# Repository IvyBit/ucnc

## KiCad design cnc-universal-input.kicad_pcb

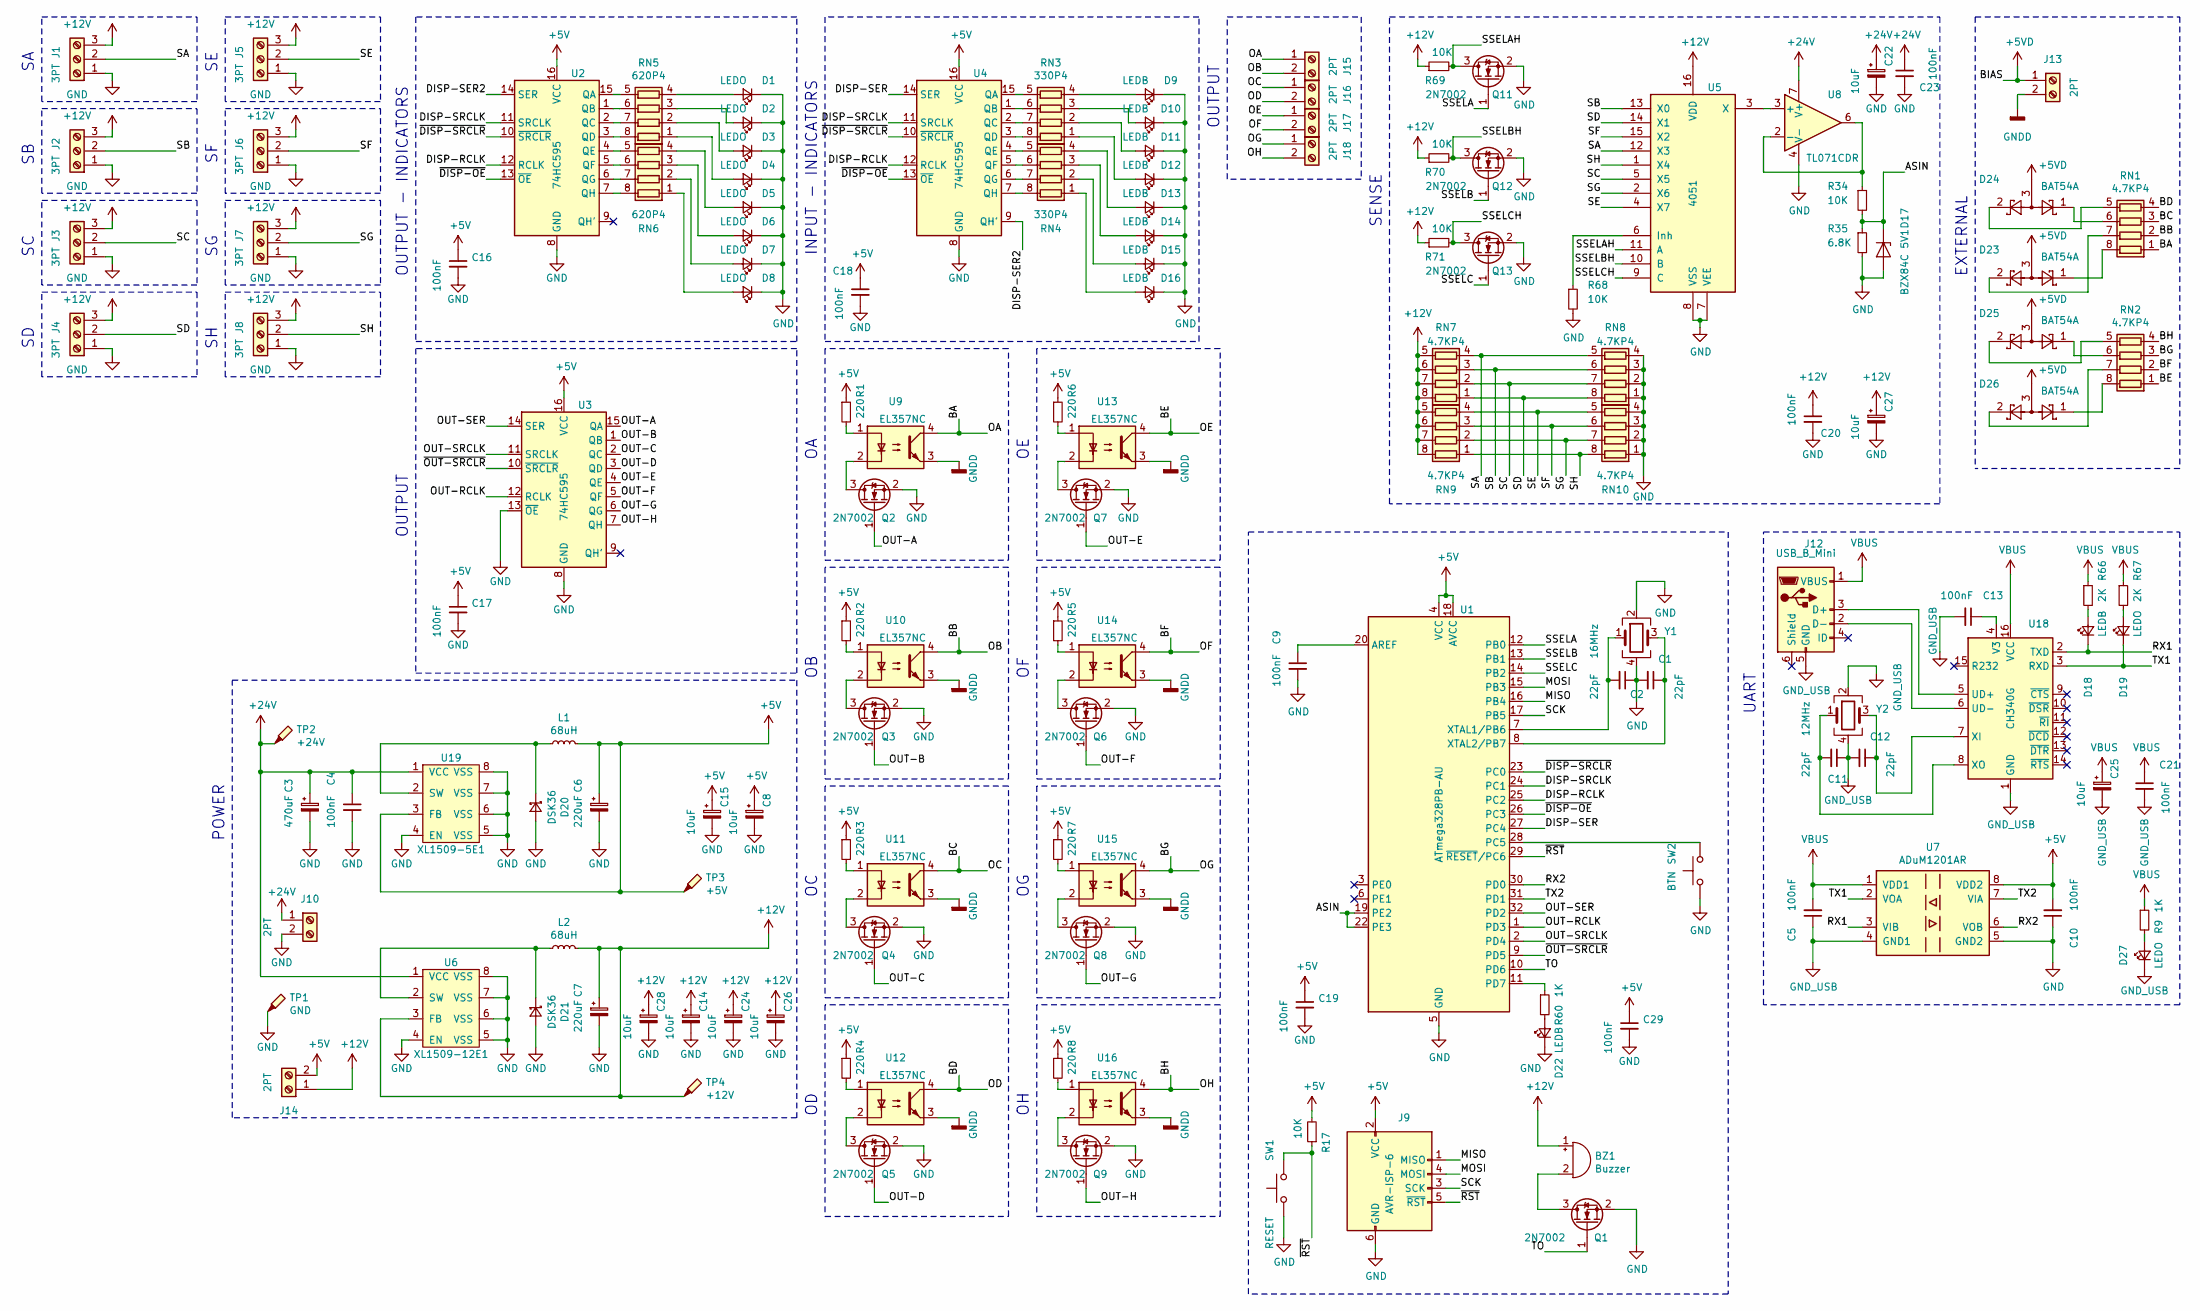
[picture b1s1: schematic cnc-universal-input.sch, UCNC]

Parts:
BZ1: Buzzer; Buzzer_15x7.5RM7.6; LCSC C128017
C1, C2, C11, C12: 22pF; C_0805_2012Metric; LCSC C1804
C3: 470uF; CP_Elec_10x10; LCSC C3350
C4, C5, C9, C10, C13, C16, C17, C18, C19, C20, C21, C23, C29: 100nF; C_0805_2012Metric; LCSC C49678
C6, C7: 220uF; CP_Elec_6.3x7.7; LCSC C3342
C8, C14, C15, C22, C24, C25, C26, C27, C28: 10uF; C_1206_3216Metric; LCSC C13585
D1, D2, D3, D4, D5, D6, D7, D8, D19, D27: LEDO; D_0805_2012Metric; LCSC C205444
D9, D10, D11, D12, D13, D14, D15, D16, D18, D22: LEDB; D_0805_2012Metric; LCSC C205441
D17: BZX84C 5V1; D_SOT-23_ANK; LCSC C294621
D20, D21: DSK36; D_SOD-123F; LCSC C106913
D23, D24, D25, D26: BAT54A; SOT-23; LCSC C556167
J1, J2, J3, J4, J5, J6, J7, J8: 3PT; TerminalBlock_RND_205-00013_1x03_P5.00mm_Horizontal; LCSC C8270
J9: AVR-ISP-6; PinHeader_2x03_P2.54mm_Vertical_SMD; LCSC C192301
J10, J13, J14, J15, J16, J17, J18: 2PT; TerminalBlock_RND_205-00001_1x02_P5.00mm_Horizontal; LCSC C8404
J12: USB_B_Mini; USB_Mini-B_Lumberg_2486_01_Horizontal; LCSC C1121886
L1, L2: 68uH; L_12x12mm_H8mm; LCSC C169377
Q1, Q2, Q3, Q4, Q5, Q6, Q7, Q8, Q9, Q11, Q12, Q13: 2N7002; SOT-23; LCSC C8545
R1, R2, R3, R4, R5, R6, R7, R8: 220; R_0805_2012Metric; LCSC C17557
R9, R60: 1K; R_0805_2012Metric; LCSC C17513
R17, R34, R68, R69, R70, R71: 10K; R_0805_2012Metric; LCSC C17724
R35: 6.8K; R_0805_2012Metric; LCSC C17772
R66, R67: 2K; R_0805_2012Metric; LCSC C17604
RN1, RN2, RN7, RN8, RN9, RN10: 4.7KP4; R_Array_Convex_4x0603; LCSC C66697
RN3, RN4: 330P4; R_Array_Convex_4x0603; LCSC C12018
RN5, RN6: 620P4; R_Array_Convex_4x0603; LCSC C12034
SW1: RESET; SW_SPST_TL3342; LCSC C318884
SW2: BTN; SW_SPST_TL3342; LCSC C318884
TP1: GND; TestPoint_Pad_D1.5mm
TP2: +24V; TestPoint_Pad_D1.5mm
TP3: +5V; TestPoint_Pad_D1.5mm
TP4: +12V; TestPoint_Pad_D1.5mm
U1: ATmega328PB-AU; TQFP-32_7x7mm_P0.8mm; LCSC C132230
U2, U3, U4: 74HC595; SOIC-16_3.9x9.9mm_P1.27mm; LCSC C5947
U5: 4051; SOIC-16_3.9x9.9mm_P1.27mm; LCSC C21379
U6: XL1509-12E1; SOIC-8_3.9x4.9mm_P1.27mm; LCSC C62594
U7: ADuM1201AR; SOIC-8_3.9x4.9mm_P1.27mm; LCSC C9669
U8: TL071CDR; SOIC-8_3.9x4.9mm_P1.27mm; LCSC C14449
U9, U10, U11, U12, U13, U14, U15, U16: EL357NC; SO-4_4.4x3.9mm_P2.54mm; LCSC C29981
U18: CH340G; SOIC-16_3.9x9.9mm_P1.27mm; LCSC C14267
U19: XL1509-5E1; SOIC-8_3.9x4.9mm_P1.27mm; LCSC C61063
Y1: 16MHz; Crystal_SMD_3225-4Pin_3.2x2.5mm; LCSC C13738
Y2: 12MHz; Crystal_SMD_3225-4Pin_3.2x2.5mm; LCSC C9002

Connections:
+5V: C6.1, C8.1, C10.2, C15.1, C16.1, C17.1, C18.1, C19.1, C29.1, J9.2 (VCC), J14.2, L1.2, R1.1, R2.1, R3.1, R4.1, R5.1, R6.1, R7.1, R8.1, R17.2, TP3.1, U1.4 (VCC), U1.18 (AVCC), U2.16 (VCC), U3.16 (VCC), U4.16 (VCC), U7.8 (VDD2), U19.3 (FB)
+5VD: D23.3, D24.3, D25.3, D26.3, J13.1
+12V: BZ1.1 (-), C7.1, C14.1, C20.1, C24.1, C26.1, C27.1, C28.1, J1.3, J2.3, J3.3, J4.3, J5.3, J6.3, J7.3, J8.3, J14.1, L2.2, R69.1, R70.1, R71.1, RN7.5 (R4.2), RN7.6 (R3.2), RN7.7 (R2.2), RN7.8 (R1.2), RN9.5 (R4.2), RN9.6 (R3.2), RN9.7 (R2.2), RN9.8 (R1.2), TP4.1, U5.16 (VDD), U6.3 (FB)
+24V: C3.1, C4.1, C22.1, C23.1, J10.1, TP2.1, U6.1 (VCC), U8.7 (V+), U19.1 (VCC)
/ASIN: D17.1 (K), R34.2, R35.1, U1.19 (PE2), U1.22 (PE3)
/BA: J15.1, RN1.1 (R1.1), U9.4
/BB: J15.2, RN1.2 (R2.1), U10.4
/BC: J16.1, RN1.3 (R3.1), U11.4
/BD: J16.2, RN1.4 (R4.1), U12.4
/BE: J17.1, RN2.1 (R1.1), U13.4
/BF: J17.2, RN2.2 (R2.1), U14.4
/BG: J18.1, RN2.3 (R3.1), U15.4
/BH: J18.2, RN2.4 (R4.1), U16.4
/DISP-RCLK: U1.25 (PC2), U2.12 (RCLK), U4.12 (RCLK)
/DISP-SER: U1.27 (PC4), U4.14 (SER)
/DISP-SER2: U2.14 (SER), U4.9 (QH')
/DISP-SRCLK: U1.24 (PC1), U2.11 (SRCLK), U4.11 (SRCLK)
/MISO: J9.1 (MISO), U1.16 (PB4)
/MOSI: J9.4 (MOSI), U1.15 (PB3)
/OUT-A: Q2.1 (G), U3.15 (QA)
/OUT-B: Q3.1 (G), U3.1 (QB)
/OUT-C: Q4.1 (G), U3.2 (QC)
/OUT-D: Q5.1 (G), U3.3 (QD)
/OUT-E: Q7.1 (G), U3.4 (QE)
/OUT-F: Q6.1 (G), U3.5 (QF)
/OUT-G: Q8.1 (G), U3.6 (QG)
/OUT-H: Q9.1 (G), U3.7 (QH)
/OUT-RCLK: U1.1 (PD3), U3.12 (RCLK)
/OUT-SER: U1.32 (PD2), U3.14 (SER)
/OUT-SRCLK: U1.2 (PD4), U3.11 (SRCLK)
/RX1: D18.1 (K), U7.3 (VIB), U18.2 (TXD)
/RX2: U1.30 (PD0), U7.6 (VOB)
/SA: J1.2, RN7.4 (R4.1), RN8.5 (R4.2), U5.12 (X3)
/SB: J2.2, RN7.3 (R3.1), RN8.6 (R3.2), U5.13 (X0)
/SC: J3.2, RN7.2 (R2.1), RN8.7 (R2.2), U5.5 (X5)
/SCK: J9.3 (SCK), U1.17 (PB5)
/SD: J4.2, RN7.1 (R1.1), RN8.8 (R1.2), U5.14 (X1)
/SE: J5.2, RN9.4 (R4.1), RN10.5 (R4.2), U5.4 (X7)
/SF: J6.2, RN9.3 (R3.1), RN10.6 (R3.2), U5.15 (X2)
/SG: J7.2, RN9.2 (R2.1), RN10.7 (R2.2), U5.2 (X6)
/SH: J8.2, RN9.1 (R1.1), RN10.8 (R1.2), U5.1 (X4)
/SSELA: Q11.1 (G), U1.12 (PB0)
/SSELAH: Q11.3 (D), R69.2, U5.11 (A)
/SSELB: Q12.1 (G), U1.13 (PB1)
/SSELBH: Q12.3 (D), R70.2, U5.10 (B)
/SSELC: Q13.1 (G), U1.14 (PB2)
/SSELCH: Q13.3 (D), R71.2, U5.9 (C)
/TO: Q1.1 (G), U1.10 (PD6)
/TX1: D19.1 (K), U7.2 (VOA), U18.3 (RXD)
/TX2: U1.31 (PD1), U7.7 (VIA)
/~DISP-OE: U1.26 (PC3), U2.13 (~OE), U4.13 (~OE)
/~DISP-SRCLR: U1.23 (PC0), U2.10 (~SRCLR), U4.10 (~SRCLR)
/~OUT-SRCLR: U1.9 (PD5), U3.10 (~SRCLR)
/~RST: J9.5 (~RST), R17.1, SW1.2, U1.29 (~RESET~/PC6)
GND: C1.2, C2.1, C3.2, C4.2, C6.2, C7.2, C8.2, C9.2, C10.1, C14.2, C15.2, C16.2, C17.2, C18.2, C19.2, C20.2, C22.2, C23.2, C24.2, C26.2, C27.2, C28.2, C29.2, D1.1 (K), D2.1 (K), D3.1 (K), D4.1 (K), D5.1 (K), D6.1 (K), D7.1 (K), D8.1 (K), D9.1 (K), D10.1 (K), D11.1 (K), D12.1 (K), D13.1 (K), D14.1 (K), D15.1 (K), D16.1 (K), D17.2 (A), D20.2 (A), D21.2 (A), D22.1 (K), J1.1, J2.1, J3.1, J4.1, J5.1, J6.1, J7.1, J8.1, J9.6 (GND), J10.2, Q1.2 (S), Q2.2 (S), Q3.2 (S), Q4.2 (S), Q5.2 (S), Q6.2 (S), Q7.2 (S), Q8.2 (S), Q9.2 (S), Q11.2 (S), Q12.2 (S), Q13.2 (S), R35.2, R68.2, RN8.1 (R1.1), RN8.2 (R2.1), RN8.3 (R3.1), RN8.4 (R4.1), RN10.1 (R1.1), RN10.2 (R2.1), RN10.3 (R3.1), RN10.4 (R4.1), SW1.1, SW2.1, TP1.1, U1.5 (GND), U1.21 (GND), U2.8 (GND), U3.8 (GND), U3.13 (~OE), U4.8 (GND), U5.7 (VEE), U5.8 (VSS), U6.4 (EN), U6.5 (VSS), U6.6 (VSS), U6.7 (VSS), U6.8 (VSS), U7.5 (GND2), U8.4 (V-), U19.4 (EN), U19.5 (VSS), U19.6 (VSS), U19.7 (VSS), U19.8 (VSS), Y1.2, Y1.4
GNDD: J13.2, U9.3, U10.3, U11.3, U12.3, U13.3, U14.3, U15.3, U16.3
GND_USB: C5.1, C11.1, C12.2, C13.2, C21.2, C25.2, D27.1 (K), J12.5 (GND), U7.4 (GND1), U18.1 (GND), Y2.2, Y2.4
unnamed: BZ1.2 (+), Q1.3 (D)
unnamed: C1.1, U1.8 (XTAL2/PB7), Y1.3
unnamed: C2.2, U1.7 (XTAL1/PB6), Y1.1
unnamed: C9.1, U1.20 (AREF)
unnamed: C11.2, U18.8 (XO), Y2.1
unnamed: C12.1, U18.7 (XI), Y2.3
unnamed: C13.1, U18.4 (V3)
unnamed: D1.2 (A), RN5.4 (R4.1)
unnamed: D2.2 (A), RN5.3 (R3.1)
unnamed: D3.2 (A), RN5.2 (R2.1)
unnamed: D4.2 (A), RN5.1 (R1.1)
unnamed: D5.2 (A), RN6.4 (R4.1)
unnamed: D6.2 (A), RN6.3 (R3.1)
unnamed: D7.2 (A), RN6.2 (R2.1)
unnamed: D8.2 (A), RN6.1 (R1.1)
unnamed: D9.2 (A), RN3.4 (R4.1)
unnamed: D10.2 (A), RN3.3 (R3.1)
unnamed: D11.2 (A), RN3.2 (R2.1)
unnamed: D12.2 (A), RN3.1 (R1.1)
unnamed: D13.2 (A), RN4.4 (R4.1)
unnamed: D14.2 (A), RN4.3 (R3.1)
unnamed: D15.2 (A), RN4.2 (R2.1)
unnamed: D16.2 (A), RN4.1 (R1.1)
unnamed: D18.2 (A), R66.2
unnamed: D19.2 (A), R67.2
unnamed: D20.1 (K), L1.1, U19.2 (SW)
unnamed: D21.1 (K), L2.1, U6.2 (SW)
unnamed: D22.2 (A), R60.2
unnamed: D23.1, RN1.8 (R1.2)
unnamed: D23.2, RN1.7 (R2.2)
unnamed: D24.1, RN1.6 (R3.2)
unnamed: D24.2, RN1.5 (R4.2)
unnamed: D25.1, RN2.6 (R3.2)
unnamed: D25.2, RN2.5 (R4.2)
unnamed: D26.1, RN2.8 (R1.2)
unnamed: D26.2, RN2.7 (R2.2)
unnamed: D27.2 (A), R9.2
unnamed: J12.2 (D-), U18.6 (UD-)
unnamed: J12.3 (D+), U18.5 (UD+)
unnamed: Q2.3 (D), U9.2
unnamed: Q3.3 (D), U10.2
unnamed: Q4.3 (D), U11.2
unnamed: Q5.3 (D), U12.2
unnamed: Q6.3 (D), U14.2
unnamed: Q7.3 (D), U13.2
unnamed: Q8.3 (D), U15.2
unnamed: Q9.3 (D), U16.2
unnamed: R1.2, U9.1
unnamed: R2.2, U10.1
unnamed: R3.2, U11.1
unnamed: R4.2, U12.1
unnamed: R5.2, U14.1
unnamed: R6.2, U13.1
unnamed: R7.2, U15.1
unnamed: R8.2, U16.1
unnamed: R34.1, U8.2 (-), U8.6
unnamed: R60.1, U1.11 (PD7)
unnamed: R68.1, U5.6 (Inh)
unnamed: RN3.5 (R4.2), U4.15 (QA)
unnamed: RN3.6 (R3.2), U4.1 (QB)
unnamed: RN3.7 (R2.2), U4.2 (QC)
unnamed: RN3.8 (R1.2), U4.3 (QD)
unnamed: RN4.5 (R4.2), U4.4 (QE)
unnamed: RN4.6 (R3.2), U4.5 (QF)
unnamed: RN4.7 (R2.2), U4.6 (QG)
unnamed: RN4.8 (R1.2), U4.7 (QH)
unnamed: RN5.5 (R4.2), U2.15 (QA)
unnamed: RN5.6 (R3.2), U2.1 (QB)
unnamed: RN5.7 (R2.2), U2.2 (QC)
unnamed: RN5.8 (R1.2), U2.3 (QD)
unnamed: RN6.5 (R4.2), U2.4 (QE)
unnamed: RN6.6 (R3.2), U2.5 (QF)
unnamed: RN6.7 (R2.2), U2.6 (QG)
unnamed: RN6.8 (R1.2), U2.7 (QH)
unnamed: SW2.2, U1.28 (PC5)
unnamed: U5.3 (X), U8.3 (+)
VBUS: C5.2, C21.1, C25.1, J12.1 (VBUS), R9.1, R66.1, R67.1, U7.1 (VDD1), U18.16 (VCC)

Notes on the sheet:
POWER
INPUT - INDICATORS
OUTPUT - INDICATORS
SENSE
EXTERNAL
OUTPUT
UART

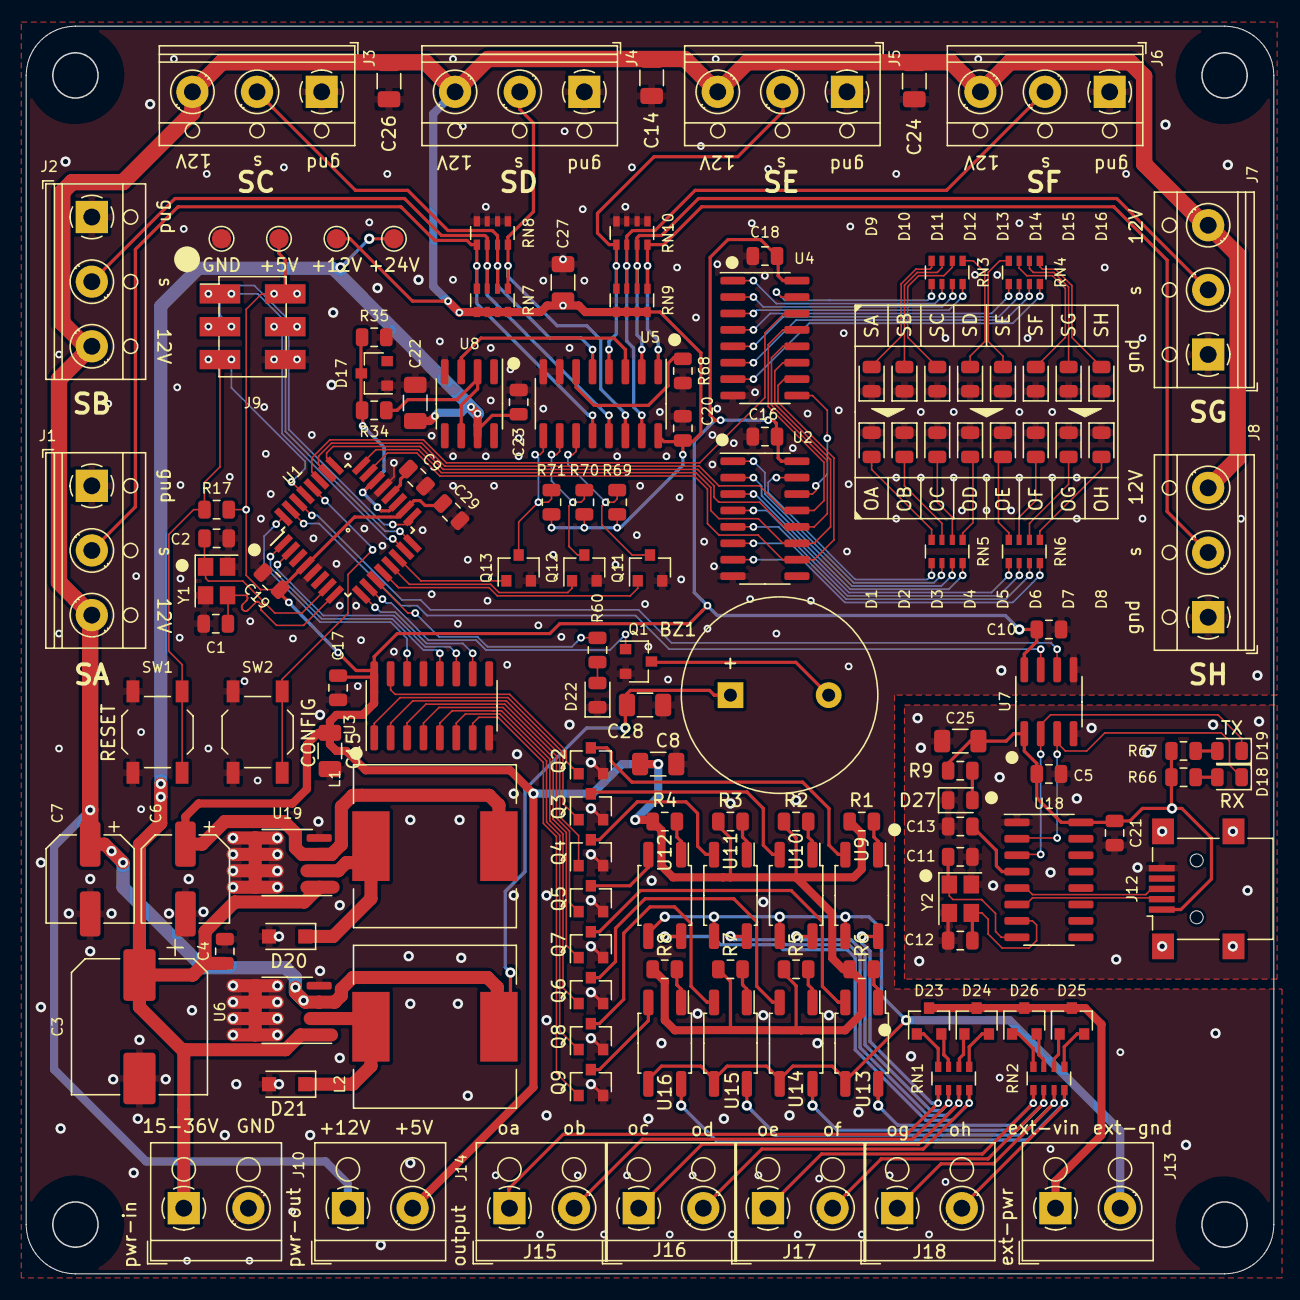
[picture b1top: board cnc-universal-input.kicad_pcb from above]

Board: 2 copper layers, 96.5 x 96.5 mm, 143 parts (0 on the bottom side), 134 nets.

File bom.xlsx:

Column1 | Column2 | Column3 | Column4
Comment | Designator | Footprint | LCSC
Buzzer | BZ1 | Buzzer_Beeper:Buzzer_15x7.5RM7.6 | C128017
22pF | C1,C2,C11,C12 | Capacitor_SMD:C_0805_2012Metric | C1804
100nF | C4,C5,C9,C10,C13,C16,C17,C18,C19,C20,C21,C23,C29 | Capacitor_SMD:C_0805_2012Metric | C49678
10uF | C8,C14,C15,C22,C24,C25,C26,C27,C28 | Capacitor_SMD:C_1206_3216Metric | C13585
470uF | C3 | Capacitor_SMD:CP_Elec_10x10 | C3350
220uF | C6,C7 | Capacitor_SMD:CP_Elec_6.3x7.7 | C3342
LEDO | D1,D2,D3,D4,D5,D6,D7,D8,D19,D27 | Diode_SMD:D_0805_2012Metric | C205444
BZX84C 5V1 | D17 | Diode_SMD:D_SOT-23_ANK | C294621
SS36-E3/57T | D20,D21 | Diode_SMD:D_2114_3652Metric | C35722
BAT54A | D23,D24,D25,D26 | Package_TO_SOT_SMD:SOT-23 | C556167
LEDB | D9,D10,D11,D12,D13,D14,D15,D16,D18,D22 | Diode_SMD:D_0805_2012Metric | C205441
3PT | J1,J2,J3,J4,J5,J6,J7,J8 | TerminalBlock_RND:TerminalBlock_RND_205-00013_1x03_P5.00mm_Horizontal | C8270
USB_B_Mini | J12 | Connector_USB:USB_Mini-B_Lumberg_2486_01_Horizontal | C1121886
2PT | J10,J13,J14,J15,J16,J17,J18 | TerminalBlock_RND:TerminalBlock_RND_205-00001_1x02_P5.00mm_Horizontal | C8404
AVR-ISP-6 | J9 | Connector_PinHeader_2.54mm:PinHeader_2x03_P2.54mm_Vertical_SMD | C192301
68uH | L1,L2 | Inductor_SMD:L_12x12mm_H8mm | C169377
2N7002 | Q1,Q2,Q3,Q4,Q5,Q6,Q7,Q8,Q9,Q11,Q12,Q13 | Package_TO_SOT_SMD:SOT-23 | C8545
220 | R1,R2,R3,R4,R5,R6,R7,R8 | Resistor_SMD:R_0805_2012Metric | C17557
10K | R17,R34,R68,R69,R70,R71 | Resistor_SMD:R_0805_2012Metric | C17724
6.8K | R35 | Resistor_SMD:R_0805_2012Metric | C17772
1K | R9,R60 | Resistor_SMD:R_0805_2012Metric | C17513
2K | R66,R67 | Resistor_SMD:R_0805_2012Metric | C17604
4.7KP4 | RN1,RN2,RN7,RN8,RN9,RN10 | Resistor_SMD:R_Array_Convex_4x0603 | C66697
330P4 | RN3,RN4 | Resistor_SMD:R_Array_Convex_4x0603 | C12018
620P4 | RN5,RN6 | Resistor_SMD:R_Array_Convex_4x0603 | C12034
RESET | SW1 | Button_Switch_SMD:SW_SPST_TL3342 | C318884
BTN | SW2 | Button_Switch_SMD:SW_SPST_TL3342 | C318884
GND | TP1 | TestPoint:TestPoint_Pad_D1.5mm
+24V | TP2 | TestPoint:TestPoint_Pad_D1.5mm
+5V | TP3 | TestPoint:TestPoint_Pad_D1.5mm
+12V | TP4 | TestPoint:TestPoint_Pad_D1.5mm
ATmega328PB-AU | U1 | Package_QFP:TQFP-32_7x7mm_P0.8mm | C132230
CH340G | U18 | Package_SO:SOIC-16_3.9x9.9mm_P1.27mm | C14267
XL1509-5E1 | U19 | Package_SO:SOIC-8_3.9x4.9mm_P1.27mm | C61063
74HC595 | U2,U3,U4 | Package_SO:SOIC-16_3.9x9.9mm_P1.27mm | C5947
4051 | U5 | Package_SO:SOIC-16_3.9x9.9mm_P1.27mm | C21379
XL1509-12E1 | U6 | Package_SO:SOIC-8_3.9x4.9mm_P1.27mm | C62594
ADuM1201AR | U7 | Package_SO:SOIC-8_3.9x4.9mm_P1.27mm | C9669
SGMOP07CXS8G/TR | U8 | Package_SO:SOIC-8_3.9x4.9mm_P1.27mm | C89712
EL357NC | U9,U10,U11,U12,U13,U14,U15,U16 | IvyBit-footprints:SOP-4_4.1x4.4x2.54P | C29981
16MHz | Y1 | Crystal:Crystal_SMD_3225-4Pin_3.2x2.5mm | C13738
12MHz | Y2 | Crystal:Crystal_SMD_3225-4Pin_3.2x2.5mm | C9002

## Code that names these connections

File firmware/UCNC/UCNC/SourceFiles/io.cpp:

/*
 * io.cpp
 *
 * Created: 06.06.2021 00:01:02
 *  Author: alrha
 */

#include "definitions.h"
#include "io.h"

#include <avr/io.h>
#include <avr/interrupt.h>
#include <avr/wdt.h>
#include <util/delay.h>
#include <avr/pgmspace.h>
#include <avr/eeprom.h>



#define DISP_SRCLR	(PINC0)
#define DISP_SRCLK	(PINC1)
#define DISP_RCLK	(PINC2)
#define DISP_OE		(PINC3)
#define DISP_SER	(PINC4)

#define BTN_AUX		(PINC5)
#define BTN_RESET	(PINC6)

#define	OUT_SER		(PIND2)
#define	OUT_RCLK	(PIND3)
#define	OUT_SRCLK	(PIND4)
#define	OUT_SRCLR	(PIND5)

#define	OUT_TONE	(PIND6)
#define	OUT_LED		(PIND7)


#define SSEL_A		(PINB0)
#define SSEL_B		(PINB1)
#define SSEL_C		(PINB2)
#define ASIN		(PINE2)




//inverted select signal
#define ASA	((uint8_t)(~0x03 & 0x07)) //011 -> 100 -> 0x04
#define ASB	((uint8_t)(~0x00 & 0x07)) //000 -> 111 -> 0x07
#define ASC	((uint8_t)(~0x05 & 0x07)) //101 -> 010 -> 0x02
#define ASD	((uint8_t)(~0x01 & 0x07)) //001 -> 110 -> 0x06
#define ASE	((uint8_t)(~0x07 & 0x07)) //111 -> 000 -> 0x00
#define ASF	((uint8_t)(~0x02 & 0x07)) //010 -> 101 -> 0x05
#define ASG	((uint8_t)(~0x06 & 0x07)) //110 -> 001 -> 0x01
#define ASH	((uint8_t)(~0x04 & 0x07)) //100 -> 011 -> 0x03




namespace io {

	const uint8_t ASI_MAP[8] PROGMEM= { ASA, ASB, ASC, ASD, ASE, ASF, ASG, ASH };
	uint32_t boot_cfg __attribute__ ((section (".noinit")));

	volatile uint8_t	adc_values[16]	= {0};
	volatile uint8_t*	adc_value_write	= nullptr;
	volatile uint8_t*	adc_value_read	= nullptr;
	volatile bool	    adc_busy		= false;

	void setup(){
		//make PINC0-4 outputs
		DDRC |= ((1 << DISP_SRCLR) | (1 << DISP_SRCLK) | (1 << DISP_RCLK) | (1 << DISP_OE) | (1 << DISP_SER));
		//make PC5 an input
		DDRC &= ~(1 << BTN_AUX);
		//set PORTC to low and enable pullup for PC5
		PORTC = (1 << BTN_AUX);
		//disable input clear
		PORTC |= (1 << DISP_SRCLR);
		//enable input indicators
		PORTC &= ~(1 << DISP_OE);

		//make PIND2-7 outputs
		DDRD |= ((1 << OUT_SER) | (1 << OUT_RCLK) | (1 << OUT_SRCLK) | (1 << OUT_SRCLR)| (1 << OUT_TONE) | (1 << OUT_LED) );
		//disable output clear
		PORTD |= (1 << OUT_SRCLR);
		//enable outputs
		//PORTD &= ~(1 << OUT_OE);

		//make PB0-PB2 outputs
		DDRB |= (1 << SSEL_A) |(1 << SSEL_B) |(1 << SSEL_C);

		DDRE = 0x00;
		PORTE |= (1 << PINE0) | (1 << PINE1);

		//select 5v reference input ADC6 and left align result
		ADMUX |= (1 << REFS0) | (1 << MUX2) | (1 << MUX1) | (1 << ADLAR);
		//enable ADC, enable interrupt, set prescaler to 16
		ADCSRA |= (1 << ADEN) | (1 << ADIE) | (1 << ADPS2)| (0 << ADPS1)| (0 << ADPS0);

		//select input A as adc source
		PORTB = (uint8_t)((PORTB & (uint8_t)~0x07) | pgm_read_byte(&ASI_MAP[0]));


		//TIMER 0 8BIT BUZZER TONE
		OCR0A = 70;
		TCCR0A |= (1 << COM0A0) | (1 << WGM01); //TOGGLE OC0A/PD6
		//TCCR0B |= (1 << CS01) | (1 << CS00);	//64 DIV PRESCLARER


		//TIMER1 16BIT BUZZER DELAY
		TCCR1A = 0x00;
		TCCR1B = (1 << WGM12); //CTC MODE NO CLOCK SOURCE
		TIMSK1 |= (1 << OCIE1A); //ENABLE TIMER1_COMPA INTERRUPT

		//TIMER3 16BIT LED
		TCCR3A = 0x00;
		TCCR3B = (1 << WGM32); //CTC MODE NO CLOCK SOURCE
		TIMSK3 |= (1 << OCIE3A); //ENABLE TIMER3_COMPA INTERRUPT



		//enable interrupts
		sei();
	}


	void set_indicators(uint16_t indicators){

		for (uint8_t i = 0; i < 16; i++)
		{
			//shift value into register
			if((indicators >> i) & 0x01){
				PORTC |= (1 << DISP_SER);
				}else{
				PORTC &= ~(1 << DISP_SER);
			}
			//clock register
			PORTC |= (1 << DISP_SRCLK);
			PORTC &= ~(1 << DISP_SRCLK);
		}

		//clock output register
		PORTC |= (1 << DISP_RCLK);
		PORTC &= ~(1 << DISP_RCLK);
	}

	void clear_indicators(){
		//clear register
		PORTC &= ~(1 << DISP_SRCLR);
		PORTC |= (1 << DISP_SRCLR);

		//clock output register
		PORTC |= (1 << DISP_RCLK);
		PORTC &= ~(1 << DISP_RCLK);
	}

	void set_outputs(uint8_t outputs){
		for (uint8_t i = 0; i < 8; i++)
		{
			//shift value into register
			if(((outputs >> i) & 0x01)){
				PORTD |= (1 << OUT_SER);
			}else{
				PORTD &= ~(1 << OUT_SER);
			}
			//clock register
			PORTD |= (1 << OUT_SRCLK);
			PORTD &= ~(1 << OUT_SRCLK);
		}

		//clock output register
		PORTD |= (1 << OUT_RCLK);
		PORTD &= ~(1 << OUT_RCLK);
	}

	void clear_outputs(){
		//clear register
		PORTD &= ~(1 << OUT_SRCLR);
		PORTD |= (1 << OUT_SRCLR);

		//clock output register
		PORTD |= (1 << OUT_RCLK);
		PORTD &= ~(1 << OUT_RCLK);
	}



	/*BUTTON*/
	ISR(PCINT1_vect){
		cli();
		set_boot_cfg_flag();
		reset_mcu();
	}

	bool get_aux_pushed(){
		return (PINC & (1 << BTN_AUX)) != (1 << BTN_AUX);
	}

	void enable_btn_reset_async(){
		PCMSK1 |= (1 << PCINT13);
		PCICR |= (1 << PCIE1);
	}

	void disable_btn_reset_async(){
		PCICR &= ~(1 << PCIE1);
		PCMSK1 &= ~(1 << PCINT13);
	}
	/*BUTTON*/


	/*ADC*/
	ISR(ADC_vect){

		static uint8_t		adc_index = 0;

		uint8_t current_index = adc_index;
		adc_index++;

		if(adc_index > 7) adc_index = 0;

		PORTB = (uint8_t)((PORTB & (uint8_t)~0x07) | pgm_read_byte(&ASI_MAP[adc_index]));

		uint8_t av = 0;

		//av |= ADCL;
		av = ADCH;//(uint16_t)(ADCH << 8);

		adc_value_write[current_index] = (uint8_t)(av * (100.0 / ADC_LIMIT));
		if(adc_value_write[current_index] > 100){
			adc_value_write[current_index] = 100;
		}

		if(adc_index < 7){
			//start conversion
			ADCSRA |= (1 << ADSC);
		}else{
			adc_busy = false;
		}
	}

	bool adc_is_busy(){
		return adc_busy;
	}

	void adc_busy_wait(){
		while(adc_busy){}
	}

	void adc_start_conversion(){

		adc_busy = true;

		//toggle adc target buffer
		if(adc_value_read != adc_values){
		   adc_value_read = &adc_values[0];
		   adc_value_write = &adc_values[8];
		}
		else{
			adc_value_read = &adc_values[8];
			adc_value_write = &adc_values[0];
		}

		//start conversion
		ADCSRA |= (1 << ADSC);
	}

	void adc_update(uint8_t (&buffer)[8]){
		for (uint8_t i = 0; i < 8; i++){
			buffer[i] = adc_value_read[i];
		}
	}
	/*ADC*/





	/*BUZZER*/
	ISR(TIMER1_COMPA_vect){
		//STOP TIMER 0 PRESCLAER
		TCCR1B = (1 << WGM12);
		//BUZZER OFF
		TCCR0B = 0x00;	//0 DIV PRESCALER
	}

	void buzzer_on_for(uint16_t milliseconds){
		if(milliseconds == 0xFFFF) milliseconds--;
		//BUZZER ON
		TCCR0B |= (1 << CS01) | (1 << CS00);	//64 DIV PRESCLARER
		//DUMB DELAY LOOP
		for (uint16_t i = 0; i < milliseconds; i++){
			_delay_ms(1);
		}
		//BUZZER OFF
		TCCR0B = 0x00;	//0 DIV PRESCLARER
	}

	void buzzer_on_for_async(uint16_t milliseconds){
		TCNT1 = 0x00;
		//((A3/B3) * C3 ) / 1000-1
		OCR1A = (((F_CPU / 1024.0) * milliseconds) / 1000.0) - 1;
		//OCR1A = (uint16_t)(milliseconds / (1000.0 / (F_CPU / 1024.0))) - 1;
		//START TIMER 1024 PRESCLAER
		TCCR1B |= ((1 <<CS12) | (1 << CS10));
		//BUZZER ON
		TCNT0 = 0x00;
		TCCR0B |= (1 << CS01) | (1 << CS00);	//64 DIV PRESCLARER
	}

	void buzzer_on(){
		TCNT0 = 0x00;
		TCCR0B |= (1 << CS01) | (1 << CS00);	//64 DIV PRESCLARER
	}

	void buzzer_on_off(){
		TCCR0B = 0x00;	//0 DIV PRESCLARER
	}
	/*BUZZER*/




	/*LED*/
	ISR(TIMER3_COMPA_vect){
		//STOP TIMER 0 PRESCLAER
		TCCR3B = (1 << WGM32);
		//BUZZER OFF
		PORTD &= ~(1 << OUT_LED);
	}

	void led_on_for(uint16_t milliseconds){
		if(milliseconds == 0xFFFF) milliseconds--;
		//BUZZER ON
		PORTD |= (1 << OUT_LED);
		//DUMB DELAY LOOP
		for (uint16_t i = 0; i < milliseconds; i++){
			_delay_ms(1);
		}
		//BUZZER OFF
		PORTD &= ~(1 << OUT_LED);
	}

	void led_on_for_async(uint16_t milliseconds){
		TCNT3 = 0x00;
		OCR3A = (uint16_t)(milliseconds / (1000.0 / (F_CPU / 1024.0)));
		//START TIMER 1024 PRESCLAER
		TCCR3B |= ((1 <<CS32) | (1 << CS30));
		//BUZZER ON
		PORTD |= (1 << OUT_LED);
	}

	void led_on(){
		PORTD |= (1 << OUT_LED);
	}

	void led_off(){
		PORTD &= ~(1 << OUT_LED);
	}
	/*LED*/



	void disable_watchdog() {
		MCUSR &= ~(1 << WDRF);
		wdt_disable();
	}

	void reset_mcu(){
		//disable interrupts
		cli();

		wdt_enable(WDTO_2S);

		while(1){
			set_indicators(0x00FF);
			_delay_ms(50);
			set_indicators(0xFF00);
			_delay_ms(50);
		}
	}





	void set_boot_cfg_flag(){
		boot_cfg = 0xDEADBEEF;
	}

	void clear_boot_cfg_flag(){
		boot_cfg = 0x00000000;
	}

	bool boot_cfg_flag_set(){
		return boot_cfg == 0xDEADBEEF;
	}
};

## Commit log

2021-01-16 ic
    Not much just bootstrapping
2021-01-17 4051s suck
    4051s exist as HC version... did you know that?
2021-01-18 Kicad is silly
2021-01-29 fixed analog read
2021-01-29 too lazy
2021-02-14 Stupid CH34G
    Stupid CH34G
2021-02-14 Revert "Stupid CH34G"
    This reverts commit 7f279e1c5784e09311cf2a8559607ba385112eda.
2021-02-14 Fixed 340G isolation issue
2021-02-16 switched to preallocated buffers
    Really doesn't matter for this project.. just a something that bugged me.
2021-02-24 had to be quick
    Had to hack something together to get the cnc running again. I think simply "refactoring" won't do it, this needs some serious work.
    Parser works.
    Expression evaluation works.
    Truth table gets generated and outputs work.
    Saving and loading works.
    Live view works.
2021-02-24 Changed the voltage divider
    Forgot to change R2 to 10K/7K so the input voltage to the adc was a bit low. 4.5 instead of 4.9.
2021-02-28 Only usability improvements
2021-02-28 updated output config
    Output config now shows total mem free, exp mem, the expression itself and
    the error messages should be a bit more user friendly.
2021-02-28 fixed issue with backspace, colors!
    Pretty colors and threshold in status screen.
    Had a fight with putty and lost...
2021-03-01 Addded menu for general config
2021-03-07 Cleanup
2021-04-09 crap!
    wrong foot print
2021-04-30 fixed labels
2021-05-08 Couldn't find a single 328PB non AU
    Atmega328PB-AU is the only 328 I could get...
2021-05-08 ups...
    Past me had the same Idea
2021-05-08 Changed Footprint
    5mm rm buzzers don't exist
2021-06-14 Yeetus deletus
2021-06-14 It's magic!
2021-06-21 8bit adc go brrrrr
2021-07-08 Board stuff
    Flipped the input polarity
2021-07-13 ofc i missed one
2021-07-24 I am speed!
    Bumped the adc clock to 1Mhz and dropped down to 8 bit.
2021-08-12 bom be gone
2021-08-13 Fixed missing and broken step files
2021-09-08 vs weirdness
2021-09-08 Fixes and doc
2021-09-17 fixed disabled outputs
2021-09-17 Cap be gone
2021-09-17 vias
    removed most vias under pads
2021-10-24 assemble all the things!
    JLCPCB please make my life easier!!
2021-11-26 Nothing! Absolutely Nothing!
2022-01-16 Keep something in stock ffs...
2022-01-26 nothing
2022-02-05 switched the 5ohm resistors with 10k ones... burn baby burn
2022-02-05 wrong opamp...
2022-02-05 We wait for no buzzers
2022-02-05 almost lost the guide...
